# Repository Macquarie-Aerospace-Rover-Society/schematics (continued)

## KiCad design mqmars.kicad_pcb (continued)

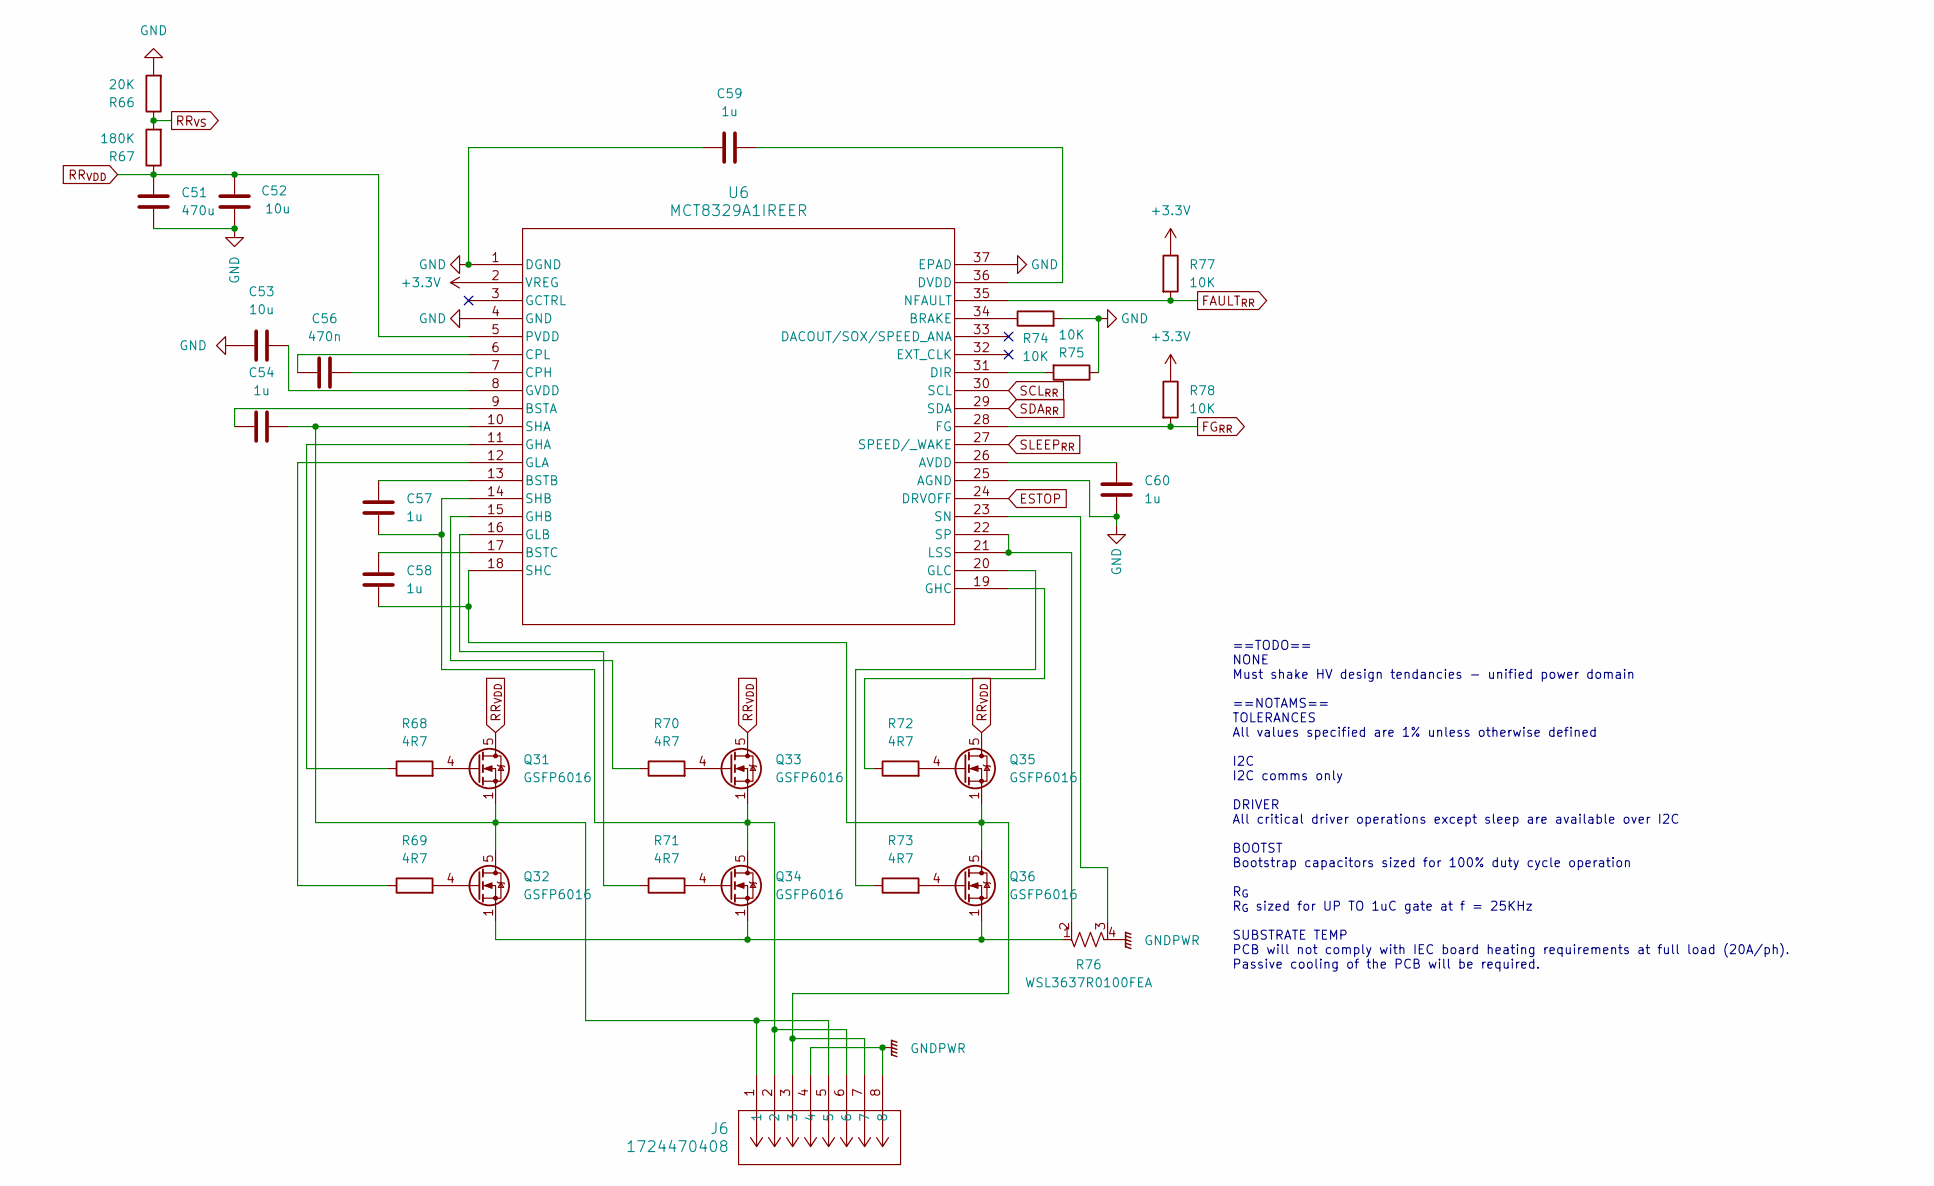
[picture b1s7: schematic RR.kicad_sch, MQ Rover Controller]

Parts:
C51: 470u; CP_Radial_D10.0mm_P5.00mm
C52: 10u; C_1210_3225Metric
C53: 10u; C_0402_1005Metric
C54, C57, C58, C59, C60: 1u; C_0201_0603Metric
C56: 470n; C_0201_0603Metric
J6: 1724470408; CONN08_1724470408_MOL
Q31, Q32, Q33, Q34, Q35, Q36: GSFP6016; PowerPAK_SO-8_Single
R66: 20K; R_0201_0603Metric
R67: 180K; R_0201_0603Metric
R68, R69, R70, R71, R72, R73: 4R7; R_0603_1608Metric
R74, R75, R77, R78: 10K; R_0201_0603Metric
R76: WSL3637R0100FEA; WSL3637_VIS
U6: MCT8329A1IREER; WQFN36_REE_TEX

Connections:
+3.3V: R77.1, R78.1, U6.2 (VREG); also elsewhere on the board
ESTOP: U6.24 (DRVOFF); also elsewhere on the board
FAULT_{RR}: R77.2, U6.35 (NFAULT); also elsewhere on the board
FG_{RR}: R78.2, U6.28 (FG)
GND: C51.2, C52.2, C53.1, C59.1, C60.1, R66.2, R74.2, R75.1, U6.1 (DGND), U6.4 (GND), U6.25 (AGND), U6.37 (EPAD); also elsewhere on the board
GNDPWR: J6.4, J6.8, R76.4; also elsewhere on the board
unnamed: Q31.4 (G), R68.2
unnamed: C54.1, J6.1, J6.5, Q31.1 (S), Q31.2 (S), Q31.3 (S), Q32.5 (D), U6.10 (SHA)
unnamed: Q32.4 (G), R69.2
unnamed: Q32.1 (S), Q32.2 (S), Q32.3 (S), Q34.1 (S), Q34.2 (S), Q34.3 (S), Q36.1 (S), Q36.2 (S), Q36.3 (S), R76.1
unnamed: Q33.4 (G), R70.2
unnamed: C57.2, J6.2, J6.6, Q33.1 (S), Q33.2 (S), Q33.3 (S), Q34.5 (D), U6.14 (SHB)
unnamed: Q34.4 (G), R71.2
unnamed: Q35.4 (G), R72.2
unnamed: C58.2, J6.3, J6.7, Q35.1 (S), Q35.2 (S), Q35.3 (S), Q36.5 (D), U6.18 (SHC)
unnamed: Q36.4 (G), R73.2
unnamed: C60.2, U6.26 (AVDD)
unnamed: R74.1, U6.34 (BRAKE)
unnamed: C54.2, U6.9 (BSTA)
unnamed: C57.1, U6.13 (BSTB)
unnamed: C58.1, U6.17 (BSTC)
unnamed: C56.1, U6.7 (CPH)
unnamed: C56.2, U6.6 (CPL)
unnamed: R75.2, U6.31 (DIR)
unnamed: C59.2, U6.36 (DVDD)
unnamed: R68.1, U6.11 (GHA)
unnamed: R70.1, U6.15 (GHB)
unnamed: R72.1, U6.19 (GHC)
unnamed: R69.1, U6.12 (GLA)
unnamed: R71.1, U6.16 (GLB)
unnamed: R73.1, U6.20 (GLC)
unnamed: C53.2, U6.8 (GVDD)
unnamed: R76.2, U6.21 (LSS), U6.22 (SP)
unnamed: R76.3, U6.23 (SN)
RR_{VDD}: C51.1, C52.1, Q31.5 (D), Q33.5 (D), Q35.5 (D), R67.1, U6.5 (PVDD); also elsewhere on the board
RR_{VS}: R66.1, R67.2; also elsewhere on the board
SCL_{RR}: U6.30 (SCL); also elsewhere on the board
SDA_{RR}: U6.29 (SDA); also elsewhere on the board
SLEEP_{RR}: U6.27 (SPEED/_WAKE)

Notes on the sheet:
==TODO== NONE Must shake HV design tendancies - unified power domain ==NOTAMS== TOLERANCES All values specified are 1% unless otherwise defined I2C I2C comms only DRIVER All critical driver operations except sleep are available over I2C BOOTST Bootstrap capacitors sized for 100% duty cycle operatio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

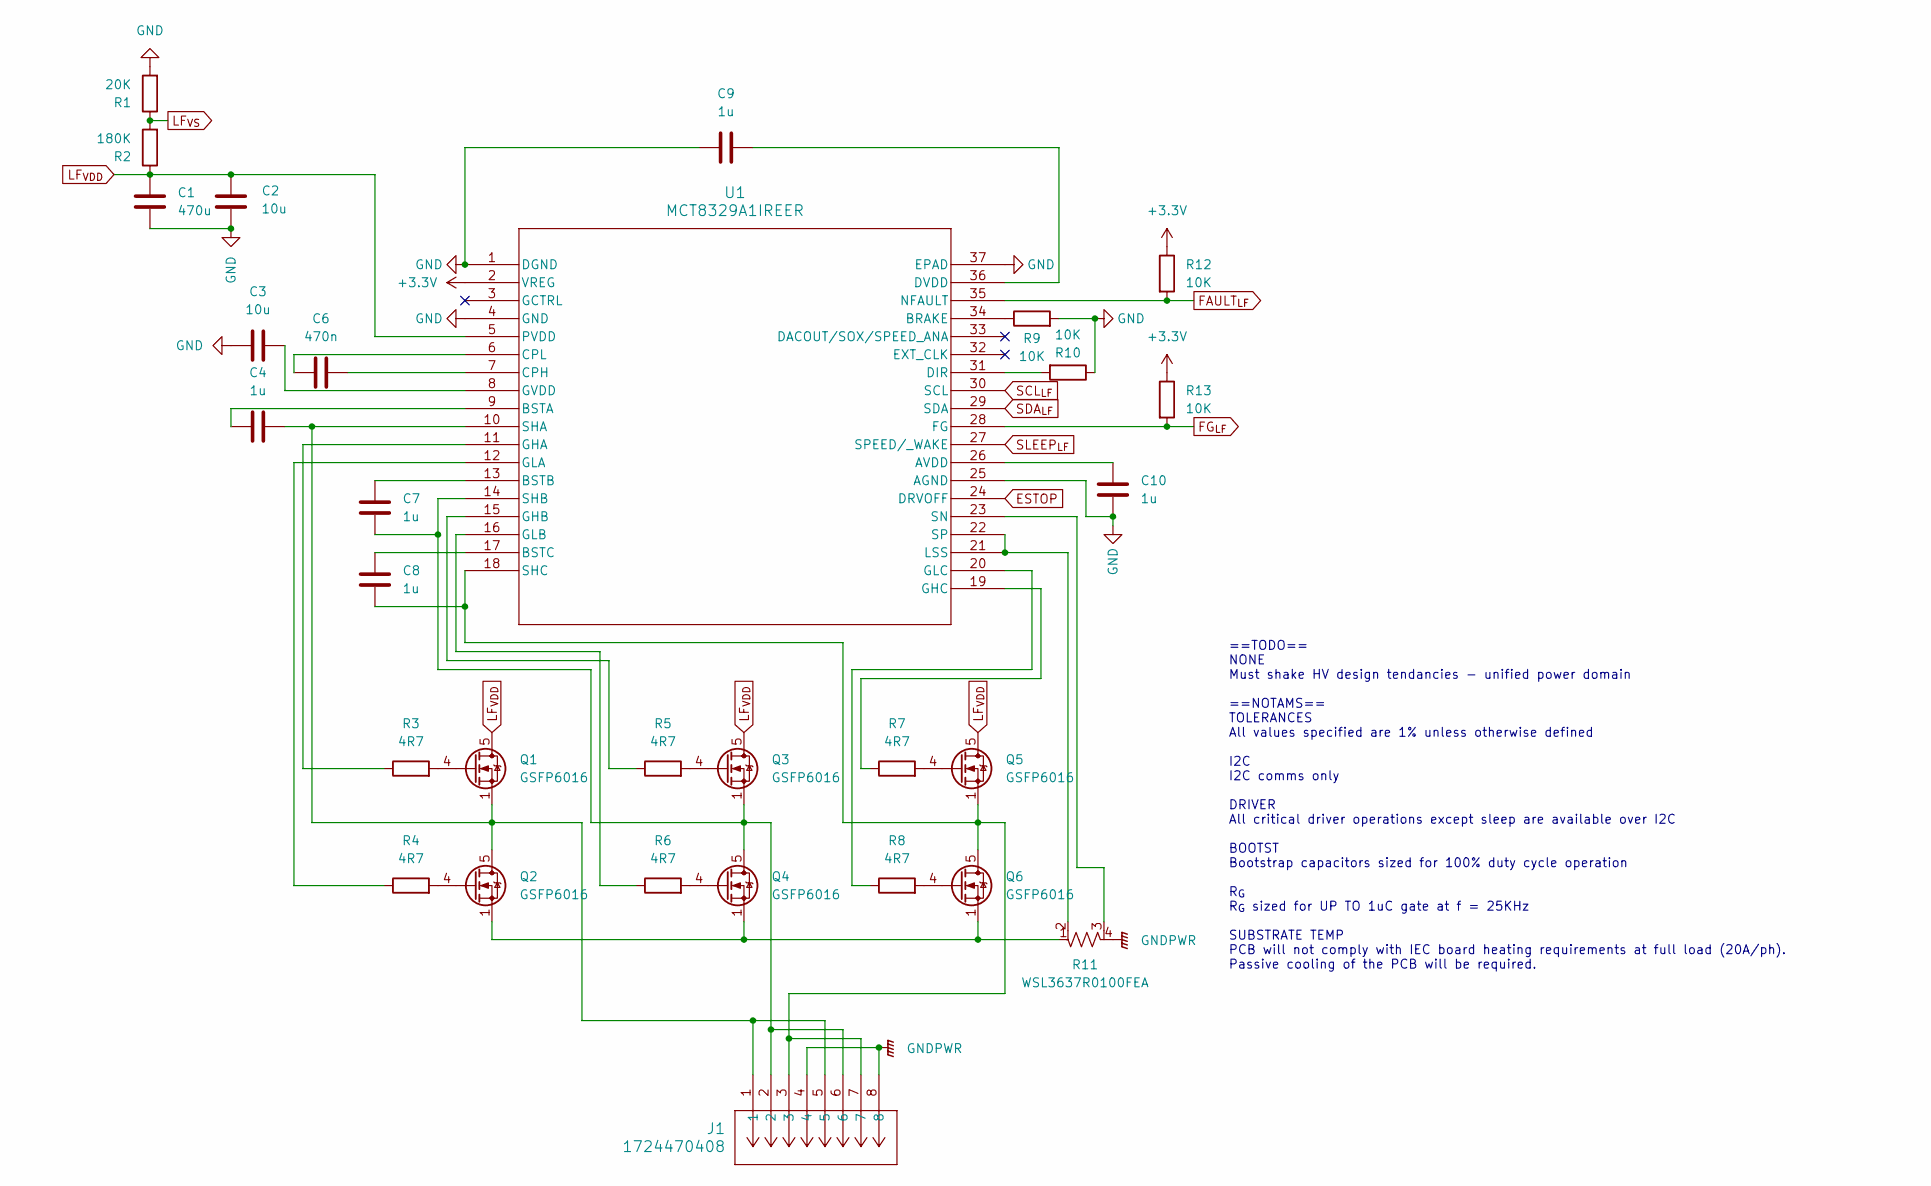
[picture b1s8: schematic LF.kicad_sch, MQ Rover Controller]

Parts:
C1: 470u; CP_Radial_D10.0mm_P5.00mm
C2: 10u; C_1210_3225Metric
C3: 10u; C_0402_1005Metric
C4, C7, C8, C9, C10: 1u; C_0201_0603Metric
C6: 470n; C_0201_0603Metric
J1: 1724470408; CONN08_1724470408_MOL
Q1, Q2, Q3, Q4, Q5, Q6: GSFP6016; PowerPAK_SO-8_Single
R1: 20K; R_0201_0603Metric
R2: 180K; R_0201_0603Metric
R3, R4, R5, R6, R7, R8: 4R7; R_0603_1608Metric
R9, R10, R12, R13: 10K; R_0201_0603Metric
R11: WSL3637R0100FEA; WSL3637_VIS
U1: MCT8329A1IREER; WQFN36_REE_TEX

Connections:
+3.3V: R12.1, R13.1, U1.2 (VREG); also elsewhere on the board
ESTOP: U1.24 (DRVOFF); also elsewhere on the board
FAULT_{LF}: R12.2, U1.35 (NFAULT); also elsewhere on the board
FG_{LF}: R13.2, U1.28 (FG)
GND: C1.2, C2.2, C3.1, C9.1, C10.1, R1.2, R9.2, R10.1, U1.1 (DGND), U1.4 (GND), U1.25 (AGND), U1.37 (EPAD); also elsewhere on the board
GNDPWR: J1.4, J1.8, R11.4; also elsewhere on the board
LF_{VDD}: C1.1, C2.1, Q1.5 (D), Q3.5 (D), Q5.5 (D), R2.1, U1.5 (PVDD); also elsewhere on the board
LF_{VS}: R1.1, R2.2; also elsewhere on the board
unnamed: Q1.4 (G), R3.2
unnamed: C4.1, J1.1, J1.5, Q1.1 (S), Q1.2 (S), Q1.3 (S), Q2.5 (D), U1.10 (SHA)
unnamed: Q2.4 (G), R4.2
unnamed: Q2.1 (S), Q2.2 (S), Q2.3 (S), Q4.1 (S), Q4.2 (S), Q4.3 (S), Q6.1 (S), Q6.2 (S), Q6.3 (S), R11.1
unnamed: Q3.4 (G), R5.2
unnamed: C7.2, J1.2, J1.6, Q3.1 (S), Q3.2 (S), Q3.3 (S), Q4.5 (D), U1.14 (SHB)
unnamed: Q4.4 (G), R6.2
unnamed: Q5.4 (G), R7.2
unnamed: C8.2, J1.3, J1.7, Q5.1 (S), Q5.2 (S), Q5.3 (S), Q6.5 (D), U1.18 (SHC)
unnamed: Q6.4 (G), R8.2
unnamed: C10.2, U1.26 (AVDD)
unnamed: R9.1, U1.34 (BRAKE)
unnamed: C4.2, U1.9 (BSTA)
unnamed: C7.1, U1.13 (BSTB)
unnamed: C8.1, U1.17 (BSTC)
unnamed: C6.1, U1.7 (CPH)
unnamed: C6.2, U1.6 (CPL)
unnamed: R10.2, U1.31 (DIR)
unnamed: C9.2, U1.36 (DVDD)
unnamed: R3.1, U1.11 (GHA)
unnamed: R5.1, U1.15 (GHB)
unnamed: R7.1, U1.19 (GHC)
unnamed: R4.1, U1.12 (GLA)
unnamed: R6.1, U1.16 (GLB)
unnamed: R8.1, U1.20 (GLC)
unnamed: C3.2, U1.8 (GVDD)
unnamed: R11.2, U1.21 (LSS), U1.22 (SP)
unnamed: R11.3, U1.23 (SN)
SCL_{LF}: U1.30 (SCL); also elsewhere on the board
SDA_{LF}: U1.29 (SDA); also elsewhere on the board
SLEEP_{LF}: U1.27 (SPEED/_WAKE); also elsewhere on the board

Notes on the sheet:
==TODO== NONE Must shake HV design tendancies - unified power domain ==NOTAMS== TOLERANCES All values specified are 1% unless otherwise defined I2C I2C comms only DRIVER All critical driver operations except sleep are available over I2C BOOTST Bootstrap capacitors sized for 100% duty cycle operatio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

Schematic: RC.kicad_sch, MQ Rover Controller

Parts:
C41: 470u; CP_Radial_D10.0mm_P5.00mm
C42: 10u; C_1210_3225Metric
C43: 10u; C_0402_1005Metric
C44, C47, C48, C49, C50: 1u; C_0201_0603Metric
C46: 470n; C_0201_0603Metric
J5: 1724470408; CONN08_1724470408_MOL
Q25, Q26, Q27, Q28, Q29, Q30: GSFP6016; PowerPAK_SO-8_Single
R53: 20K; R_0201_0603Metric
R54: 180K; R_0201_0603Metric
R55, R56, R57, R58, R59, R60: 4R7; R_0603_1608Metric
R61, R62, R64, R65: 10K; R_0201_0603Metric
R63: WSL3637R0100FEA; WSL3637_VIS
U5: MCT8329A1IREER; WQFN36_REE_TEX

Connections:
+3.3V: R64.1, R65.1, U5.2 (VREG); also elsewhere on the board
ESTOP: U5.24 (DRVOFF); also elsewhere on the board
FAULT_{RC}: R64.2, U5.35 (NFAULT); also elsewhere on the board
FG_{RC}: R65.2, U5.28 (FG)
GND: C41.2, C42.2, C43.1, C49.1, C50.1, R53.2, R61.2, R62.1, U5.1 (DGND), U5.4 (GND), U5.25 (AGND), U5.37 (EPAD); also elsewhere on the board
GNDPWR: J5.4, J5.8, R63.4; also elsewhere on the board
unnamed: Q25.4 (G), R55.2
unnamed: C44.1, J5.1, J5.5, Q25.1 (S), Q25.2 (S), Q25.3 (S), Q26.5 (D), U5.10 (SHA)
unnamed: Q26.4 (G), R56.2
unnamed: Q26.1 (S), Q26.2 (S), Q26.3 (S), Q28.1 (S), Q28.2 (S), Q28.3 (S), Q30.1 (S), Q30.2 (S), Q30.3 (S), R63.1
unnamed: Q27.4 (G), R57.2
unnamed: C47.2, J5.2, J5.6, Q27.1 (S), Q27.2 (S), Q27.3 (S), Q28.5 (D), U5.14 (SHB)
unnamed: Q28.4 (G), R58.2
unnamed: Q29.4 (G), R59.2
unnamed: C48.2, J5.3, J5.7, Q29.1 (S), Q29.2 (S), Q29.3 (S), Q30.5 (D), U5.18 (SHC)
unnamed: Q30.4 (G), R60.2
unnamed: C50.2, U5.26 (AVDD)
unnamed: R61.1, U5.34 (BRAKE)
unnamed: C44.2, U5.9 (BSTA)
unnamed: C47.1, U5.13 (BSTB)
unnamed: C48.1, U5.17 (BSTC)
unnamed: C46.1, U5.7 (CPH)
unnamed: C46.2, U5.6 (CPL)
unnamed: R62.2, U5.31 (DIR)
unnamed: C49.2, U5.36 (DVDD)
unnamed: R55.1, U5.11 (GHA)
unnamed: R57.1, U5.15 (GHB)
unnamed: R59.1, U5.19 (GHC)
unnamed: R56.1, U5.12 (GLA)
unnamed: R58.1, U5.16 (GLB)
unnamed: R60.1, U5.20 (GLC)
unnamed: C43.2, U5.8 (GVDD)
unnamed: R63.2, U5.21 (LSS), U5.22 (SP)
unnamed: R63.3, U5.23 (SN)
RC_{VDD}: C41.1, C42.1, Q25.5 (D), Q27.5 (D), Q29.5 (D), R54.1, U5.5 (PVDD); also elsewhere on the board
RC_{VS}: R53.1, R54.2; also elsewhere on the board
SCL_{RC}: U5.30 (SCL); also elsewhere on the board
SDA_{RC}: U5.29 (SDA); also elsewhere on the board
SLEEP_{RC}: U5.27 (SPEED/_WAKE)

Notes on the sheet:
==TODO== NONE Must shake HV design tendancies - unified power domain ==NOTAMS== TOLERANCES All values specified are 1% unless otherwise defined I2C I2C comms only DRIVER All critical driver operations except sleep are available over I2C BOOTST Bootstrap capacitors sized for 100% duty cycle operatio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

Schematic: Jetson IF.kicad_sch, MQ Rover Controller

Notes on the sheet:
==TODO== SCHEMATICS Communications protocol to be determined ==NOTAMS== NONE

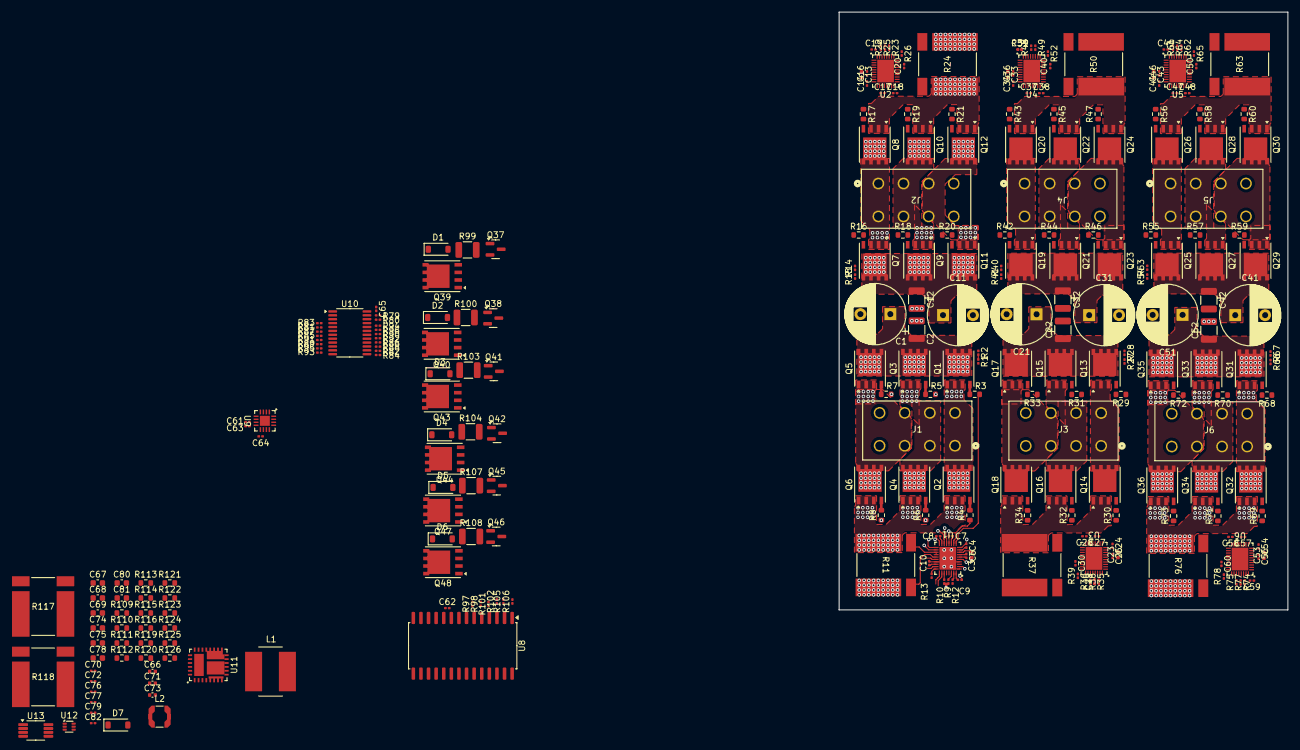
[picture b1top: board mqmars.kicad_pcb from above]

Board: 4 copper layers, 75.0 x 99.9 mm, 277 parts (0 on the bottom side), 268 nets.

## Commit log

2024-12-24 Revision A
    Initial upload - decisions pending
2024-12-24 moved some designators to identify pullup resistors
2024-12-26 The great decluttering
    Moved all possible controls to I2C, part selection commenced, IOs assigned pending comms schema
2024-12-28 Powerstage
    Powerstage layout, non critical changes to schematic
